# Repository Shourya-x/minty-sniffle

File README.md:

# 🍬👃 Minty-Sniffle

**Ultra-compact, coin-cell-powered BLE environmental node for continuous room heatmapping and fire detection.**

## Overview
Minty-Sniffle is a hardware engineering challenge designed from CAD to ECAD in a single day. The goal is to pack an AI-enabled gas sensor, a Bluetooth Low Energy (BLE) microcontroller, and a high-capacity coin cell battery into a custom 3D-printed enclosure measuring just 50mm x 30mm x 15mm (a slightly beefed-up Tic Tac box). 

By deploying multiple Minty-Sniffle nodes across a space, the network can triangulate gas leaks, detect early-stage fires, and generate real-time environmental heatmaps via BLE mesh communication.

## Hardware Architecture
*   **Microcontroller:** nRF52840 (or nRF52833) for ultra-low-power BLE and long-range coded PHY.
*   **Gas Sensor:** Bosch BME688 (4-in-1 AI gas, pressure, temperature, and humidity sensor).
*   **Power Source:** CR2477 Coin Cell Battery (3V, ~1000mAh) with a large bypass capacitor to handle BME688 heater pulses without browning out the MCU.
*   **Enclosure:** Custom 3D printed shell with dedicated airflow channels and louvers for maximum sensor exposure.

## Key Features
*   **AI Gas Scanning:** Utilizing BME AI-Studio to train the sensor to recognize specific VOC footprints and fire precursors.
*   **Duty-Cycled Power:** Sensor heater is pulsed optimally to allow months of continuous run time on a single CR2477.
*   **BLE Mesh Ready:** Nodes broadcast sensor payloads to a central gateway for room-scale heatmapping.

## Repository Structure
*   `/website/` - Interactive Astro + Three.js hardware showcase, 3D enclosure/PCBA studio, soft-latch simulator, and digital datasheet.
*   `/hardware/kicad/` - KiCad 9 schematic, 2-layer PCB layout, and JLCPCB manufacturing archives.
*   `/hardware/cad/` - FreeCAD parametric enclosure models (`.FCStd`), STEP assembly, and 3D-printable `.STL` files.
*   `/datasheets/` - Component reference PDF datasheets (Holyiot nRF52840, Bosch BME680, SD3031 RTC, FM24CL16B FRAM).
*   `/docs/` - Architecture notes, power calculations, and hardware documentation.
*   `/firmware/` - nRF52 C/C++ source code, BLE stack configurations, and sensor driver integration.

## Development Sprint Log
- **Phase 1:** MCAD physical bounding box and DXF export (50x30x15mm).
- **Phase 2:** ECAD schematic capture (nRF52 + BME688 + CR2477 power delivery).
- **Phase 3:** PCB layout, thermal isolation of the sensor, and component placement.
- **Phase 4:** MCAD enclosure detailing (ventilation design, snap-fits).

---
*Created by Shourya Pandey*

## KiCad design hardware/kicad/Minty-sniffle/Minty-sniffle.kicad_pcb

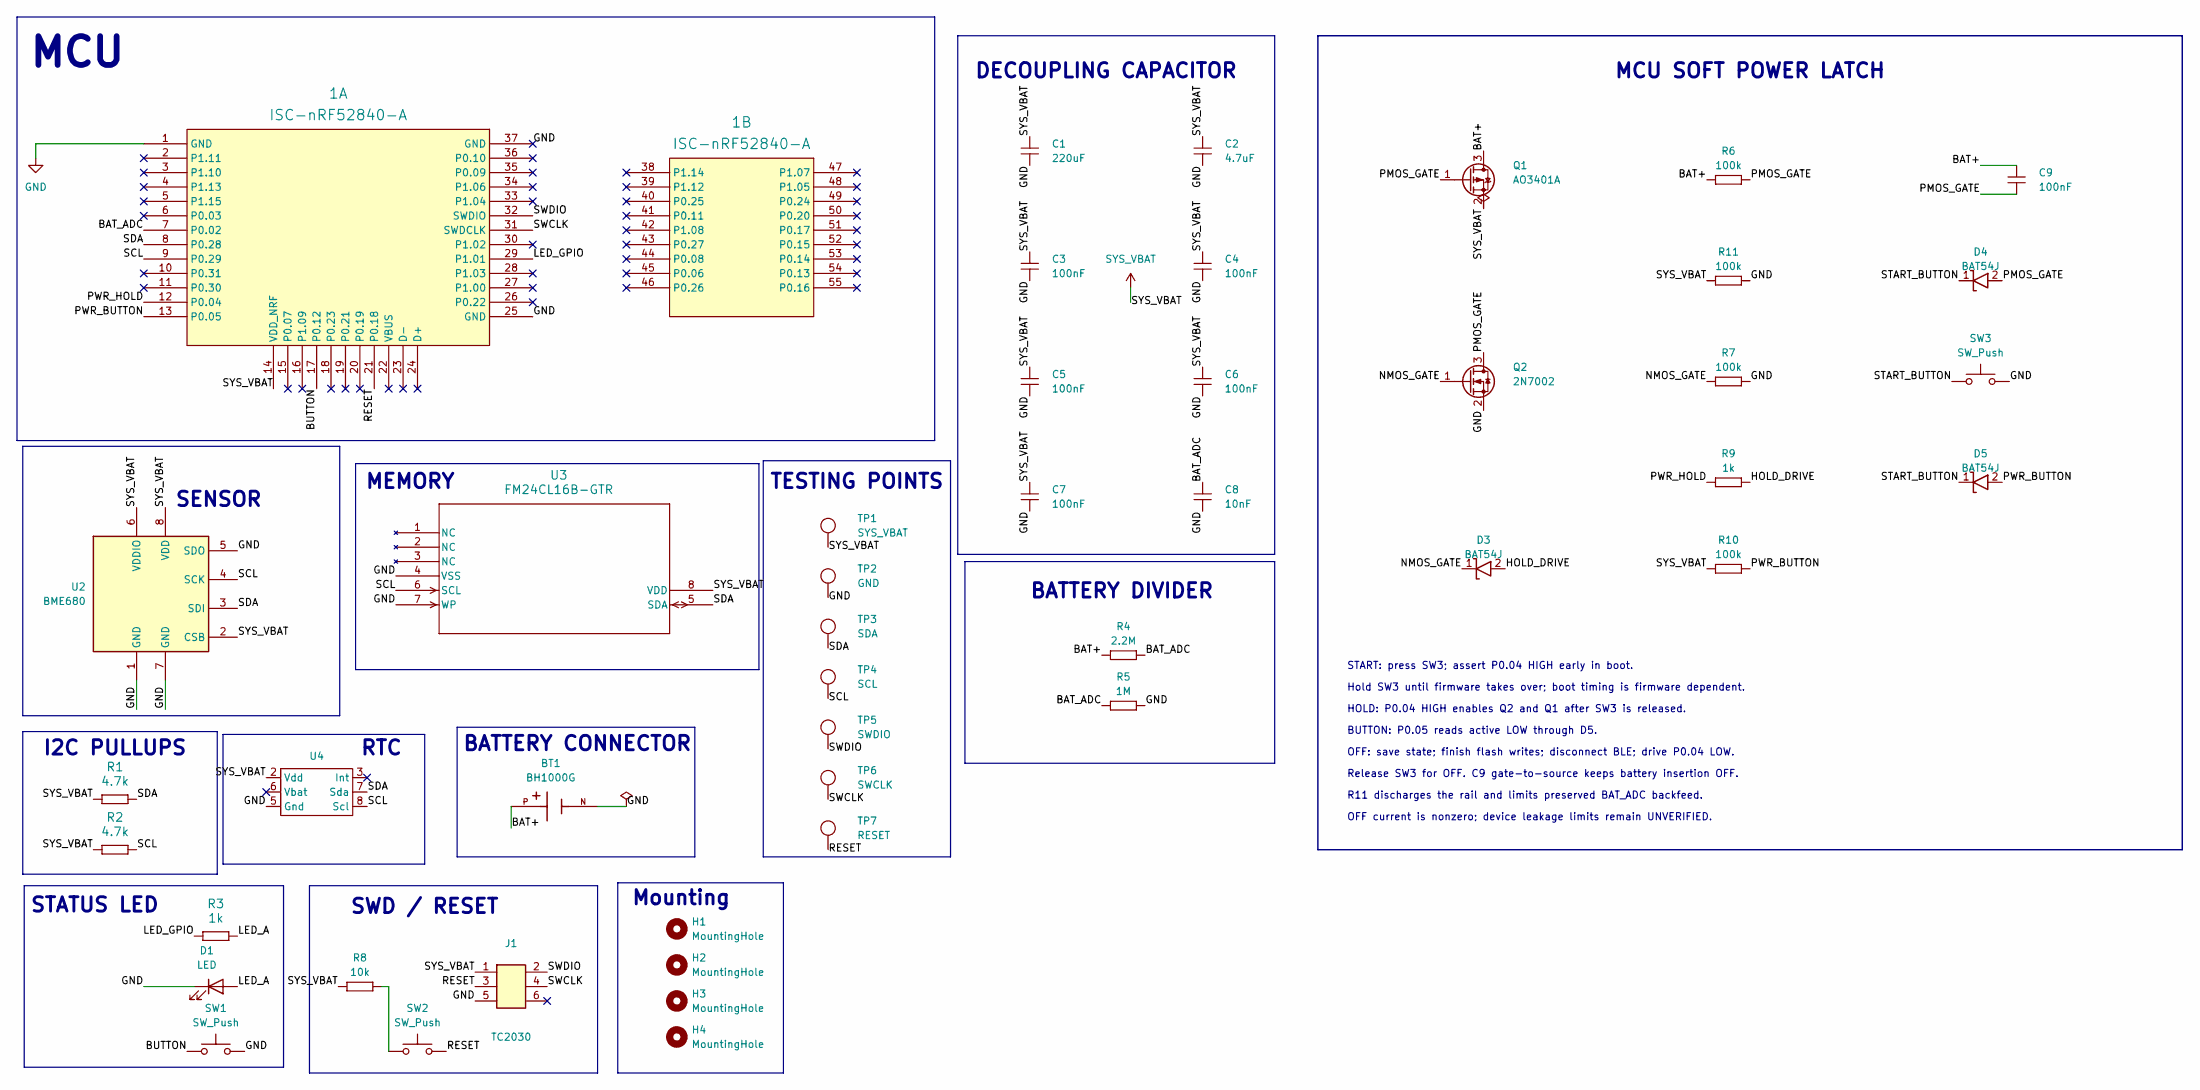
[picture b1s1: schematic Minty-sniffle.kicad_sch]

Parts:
1: ISC-nRF52840-A; ISC-nRF52840-MODULE
BT1: BH1000G; BAT_BH1000G; PARTREV E
C1: 220uF; Capacitor_SMD__C_1206_3216Metric_Pad1.33x1.80mm_HandSolder_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
C2: 4.7uF; Capacitor_SMD__C_1206_3216Metric_Pad1.33x1.80mm_HandSolder_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
C3, C4, C5, C6, C7, C9: 100nF; Capacitor_SMD__C_1206_3216Metric_Pad1.33x1.80mm_HandSolder_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
C8: 10nF; Capacitor_SMD__C_1206_3216Metric_Pad1.33x1.80mm_HandSolder_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
D1: LED; LED_SMD__LED_1206_3216Metric_Pad1.42x1.75mm_HandSolder_5459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
D3, D4, D5: BAT54J; Diode_SMD__D_SOD-323_14c7701009
H1, H2, H3, H4: MountingHole; MountingHole__MountingHole_2.2mm_M2_f6c03cebac
J1: TC2030; Connector__Tag-Connect_TC2030-IDC-NL_2x03_P1.27mm_Vertical_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
Q1: AO3401A; Package_TO_SOT_SMD__SOT-23_e3fc7a82cd
Q2: 2N7002; Package_TO_SOT_SMD__SOT-23_e3fc7a82cd
R1, R2: 4.7k; Resistor_SMD__R_1206_3216Metric_Pad1.30x1.75mm_HandSolder_5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
R3, R9: 1k; Resistor_SMD__R_1206_3216Metric_Pad1.30x1.75mm_HandSolder_5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
R4: 2.2M; Resistor_SMD__R_1206_3216Metric_Pad1.30x1.75mm_HandSolder_5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
R5: 1M; Resistor_SMD__R_1206_3216Metric_Pad1.30x1.75mm_HandSolder_5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
R6, R7, R10, R11: 100k; Resistor_SMD__R_1206_3216Metric_Pad1.30x1.75mm_HandSolder_5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
R8: 10k; Resistor_SMD__R_1206_3216Metric_Pad1.30x1.75mm_HandSolder_5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
SW1, SW2, SW3: SW_Push; B3U-1000P
TP1: SYS_VBAT; TestPoint__TestPoint_Pad_D1.0mm_9a299b34f1
TP2: GND; TestPoint__TestPoint_Pad_D1.0mm_9a299b34f1
TP3: SDA; TestPoint__TestPoint_Pad_D1.0mm_9a299b34f1
TP4: SCL; TestPoint__TestPoint_Pad_D1.0mm_9a299b34f1
TP5: SWDIO; TestPoint__TestPoint_Pad_D1.0mm_9a299b34f1
TP6: SWCLK; TestPoint__TestPoint_Pad_D1.0mm_9a299b34f1
TP7: RESET; TestPoint__TestPoint_Pad_D1.0mm_9a299b34f1
U2: BME680; Package_LGA__Bosch_LGA-8_3x3mm_P0.8mm_ClockwisePinNumbering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
U3: FM24CL16B-GTR; SOIC-8
U4: Package_SO__SOIC-8_5.3x5.3mm_P1.27mm_29768ff8c2

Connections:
/BAT+: BT1.P, C9.1, Q1.3 (D), R4.1, R6.1
/BAT_ADC: 1.7 (P0.02), C8.1, R4.2, R5.1
/BUTTON: 1.17 (P0.12), SW1.1
/HOLD_DRIVE: D3.2 (A), R9.2
/LED_A: D1.2 (A), R3.2
/LED_GPIO: 1.29 (P1.01), R3.1
/NMOS_GATE: D3.1 (K), Q2.1 (G), R7.1
/PMOS_GATE: C9.2, D4.2 (A), Q1.1 (G), Q2.3 (D), R6.2
/PWR_BUTTON: 1.13 (P0.05), D5.2 (A), R10.2
/PWR_HOLD: 1.12 (P0.04), R9.1
/RESET: 1.21 (P0.18), J1.3, SW2.2, TP7.1 (1_1)
/SCL: 1.9 (P0.29), R2.2, TP4.1 (1_1), U2.4 (SCK), U3.6 (SCL), U4.8 (Scl)
/SDA: 1.8 (P0.28), R1.2, TP3.1 (1_1), U2.3 (SDI), U3.5 (SDA), U4.7 (Sda)
/START_BUTTON: D4.1 (K), D5.1 (K), SW3.1
/SWCLK: 1.31 (SWDCLK), J1.4, TP6.1 (1_1)
/SWDIO: 1.32 (SWDIO), J1.2, TP5.1 (1_1)
GND: 1.1 (GND), 1.25 (GND), 1.37 (GND), BT1.N, C1.2, C2.2, C3.2, C4.2, C5.2, C6.2, C7.2, C8.2, D1.1 (K), J1.5, Q2.2 (S), R5.2, R7.2, R11.2, SW1.2, SW3.2, TP2.1 (1_1), U2.1 (GND), U2.5 (SDO), U2.7 (GND), U3.4 (VSS), U3.7 (WP), U4.5 (Gnd)
unnamed: R8.2, SW2.1
SYS_VBAT: 1.14 (VDD_NRF), C1.1, C2.1, C3.1, C4.1, C5.1, C6.1, C7.1, J1.1, Q1.2 (S), R1.1, R2.1, R8.1, R10.1, R11.1, TP1.1 (1_1), U2.2 (CSB), U2.6 (VDDIO), U2.8 (VDD), U3.8 (VDD), U4.2 (Vdd)

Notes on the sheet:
MCU
MCU SOFT POWER LATCH
START: press SW3; assert P0.04 HIGH early in boot.
Hold SW3 until firmware takes over; boot timing is firmware dependent.
HOLD: P0.04 HIGH enables Q2 and Q1 after SW3 is released.
BUTTON: P0.05 reads active LOW through D5.
OFF: save state; finish flash writes; disconnect BLE; drive P0.04 LOW.
Release SW3 for OFF. C9 gate-to-source keeps battery insertion OFF.
R11 discharges the rail and limits preserved BAT_ADC backfeed.
OFF current is nonzero; device leakage limits remain UNVERIFIED.
DECOUPLING CAPACITOR
BATTERY DIVIDER
SWD / RESET
TESTING POINTS
SENSOR
RTC
BATTERY CONNECTOR
I2C PULLUPS
STATUS LED
MEMORY
Mounting

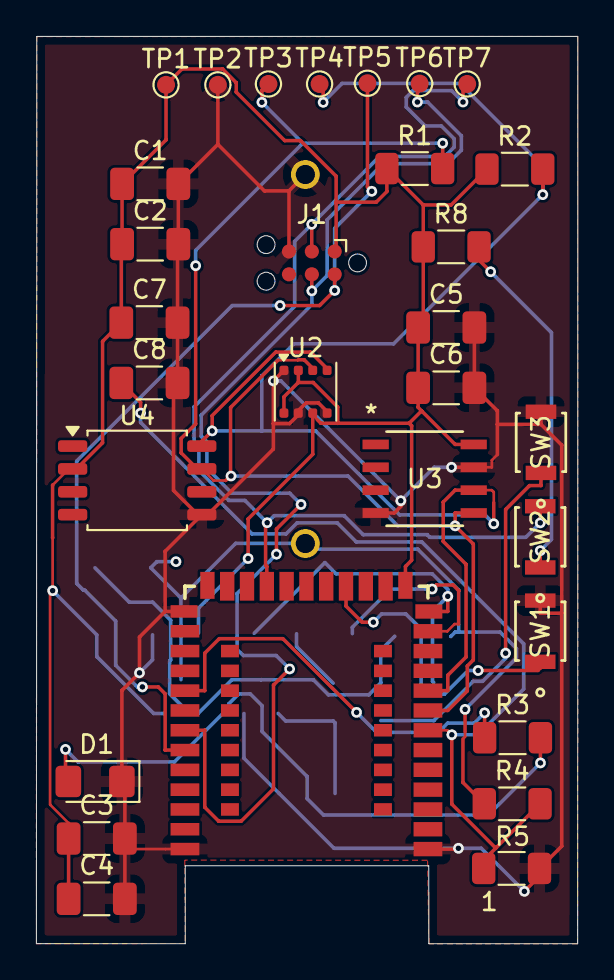
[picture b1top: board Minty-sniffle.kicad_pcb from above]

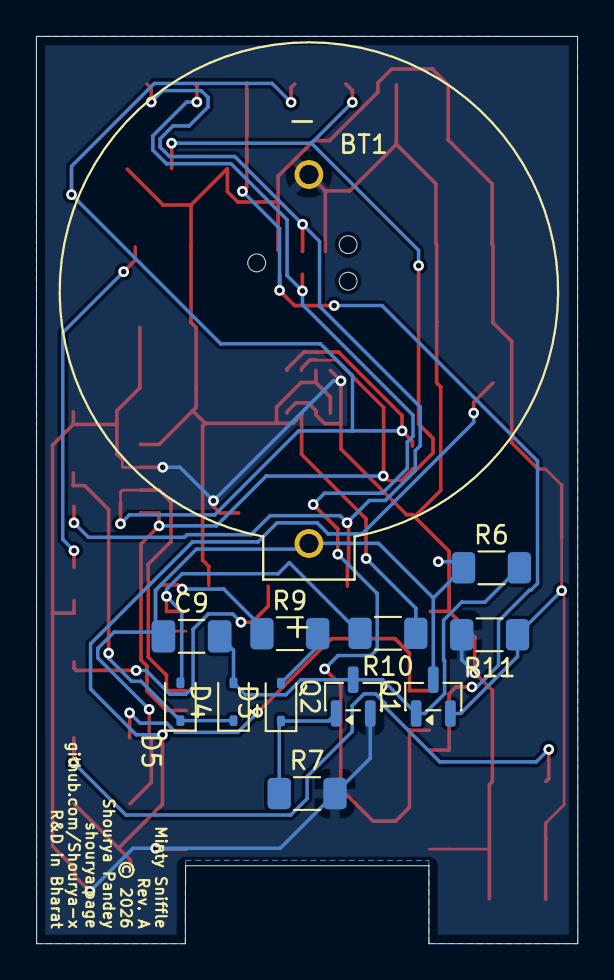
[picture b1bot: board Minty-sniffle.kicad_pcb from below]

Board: 2 copper layers, 30.1 x 50.4 mm, 42 parts (12 on the bottom side), 19 nets.

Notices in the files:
hardware/kicad/Minty-sniffle/Minty-sniffle.kicad_pcb:
© 2026
